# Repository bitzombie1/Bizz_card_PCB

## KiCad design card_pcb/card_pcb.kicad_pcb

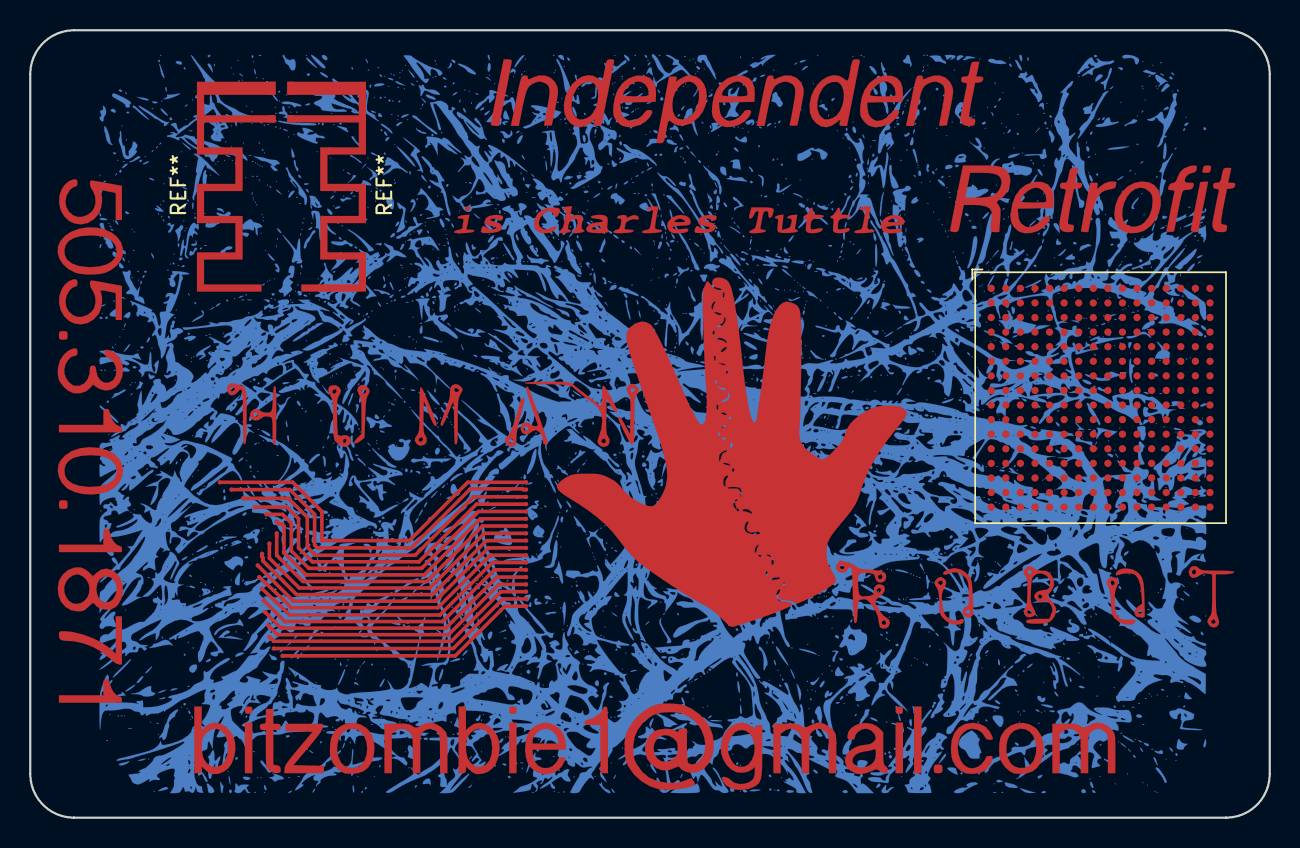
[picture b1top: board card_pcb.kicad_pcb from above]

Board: 2 copper layers, 85.0 x 54.0 mm, 40 parts (0 on the bottom side), 18 nets.

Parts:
G1: LOGO; hand
G2: LOGO; phone
G3: LOGO; email
G4: LOGO; indy_retro
TP1, TP2, TP3, TP4, TP5, TP6, TP7, TP8, TP9, TP10, TP11, TP12, TP13, TP14, TP15, TP16, TP17, TP18, TP19, TP20, TP21, TP22, TP23, TP24, TP25, TP26, TP27, TP28, TP29, TP30, TP31, TP32, TP33, TP34, TP35, TP36: TestPoint; little_pad

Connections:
unnamed: TP1.1, TP2.1
unnamed: TP3.1, TP8.1
unnamed: TP4.1, TP9.1
unnamed: TP5.1, TP10.1
unnamed: TP6.1, TP11.1
unnamed: TP7.1, TP12.1
unnamed: TP13.1, TP19.1
unnamed: TP14.1, TP20.1
unnamed: TP15.1, TP21.1
unnamed: TP16.1, TP22.1
unnamed: TP17.1, TP23.1
unnamed: TP18.1, TP24.1
unnamed: TP25.1, TP31.1
unnamed: TP26.1, TP32.1
unnamed: TP27.1, TP33.1
unnamed: TP28.1, TP34.1
unnamed: TP29.1, TP35.1
unnamed: TP30.1, TP36.1

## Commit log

2018-10-15 Rainy Sunday
2018-10-15 a trim off the top
